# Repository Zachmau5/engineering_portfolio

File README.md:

# Zachary Hallett – Engineering Portfolio

Technical portfolio containing non-proprietary engineering projects focused on RF systems, satellite communications, DSP, embedded systems, FPGA development, scientific computing, and aerospace-related software development. The projects in this repository were developed through undergraduate electrical engineering research, independent technical work, and hands-on experimentation with real-world hardware and software systems.

---

# Areas of Interest

- RF Systems & SDR
- Satellite Communications
- Digital Signal Processing (DSP)
- Embedded Systems
- FPGA / VHDL Development
- Aerospace Systems
- Orbital Mechanics & Tracking
- Python Engineering Tools
- Real-Time Control Systems
- Linux-Based Engineering Workflows

---

# Repository Structure

```text
/amsat-ground-station
    Portable SDR-based amateur satellite tracking and ground station system

/kicad_projects
    Dump of personal KiCad designs and documents

---

# Featured Project – AMSAT Portable Ground Station

A portable dual-band amateur satellite ground station integrating:

- Automated antenna tracking
- Real-time orbit propagation
- SDR hardware integration
- RF subsystem analysis
- Autonomous azimuth/elevation control
- GUI-based visualization and tracking
- Satellite pass prediction
- Coordinate transformation pipelines
- Real-time tracking-control algorithms

## Key Technologies

- Python
- Skyfield / SGP4
- GNU Radio
- SDR platforms
- GS-232B rotator control
- RF front-end integration
- Real-time control systems

---

# Tools & Technologies

## Languages

- Python
- C / C++
- VHDL

## Engineering Tools

- LTSpice
- GNU Radio
- Vivado
- Git
- Linux
- KiCad

## Technical Areas

- SDR
- SATCOM
- DSP
- RF Analysis
- FPGA
- Embedded Systems
- Orbital Mechanics
- Real-Time Systems

---

# Notes

All material contained in this repository is non-proprietary and intended for educational, research, and portfolio purposes only. No export-controlled, classified, or employer-proprietary information is included.

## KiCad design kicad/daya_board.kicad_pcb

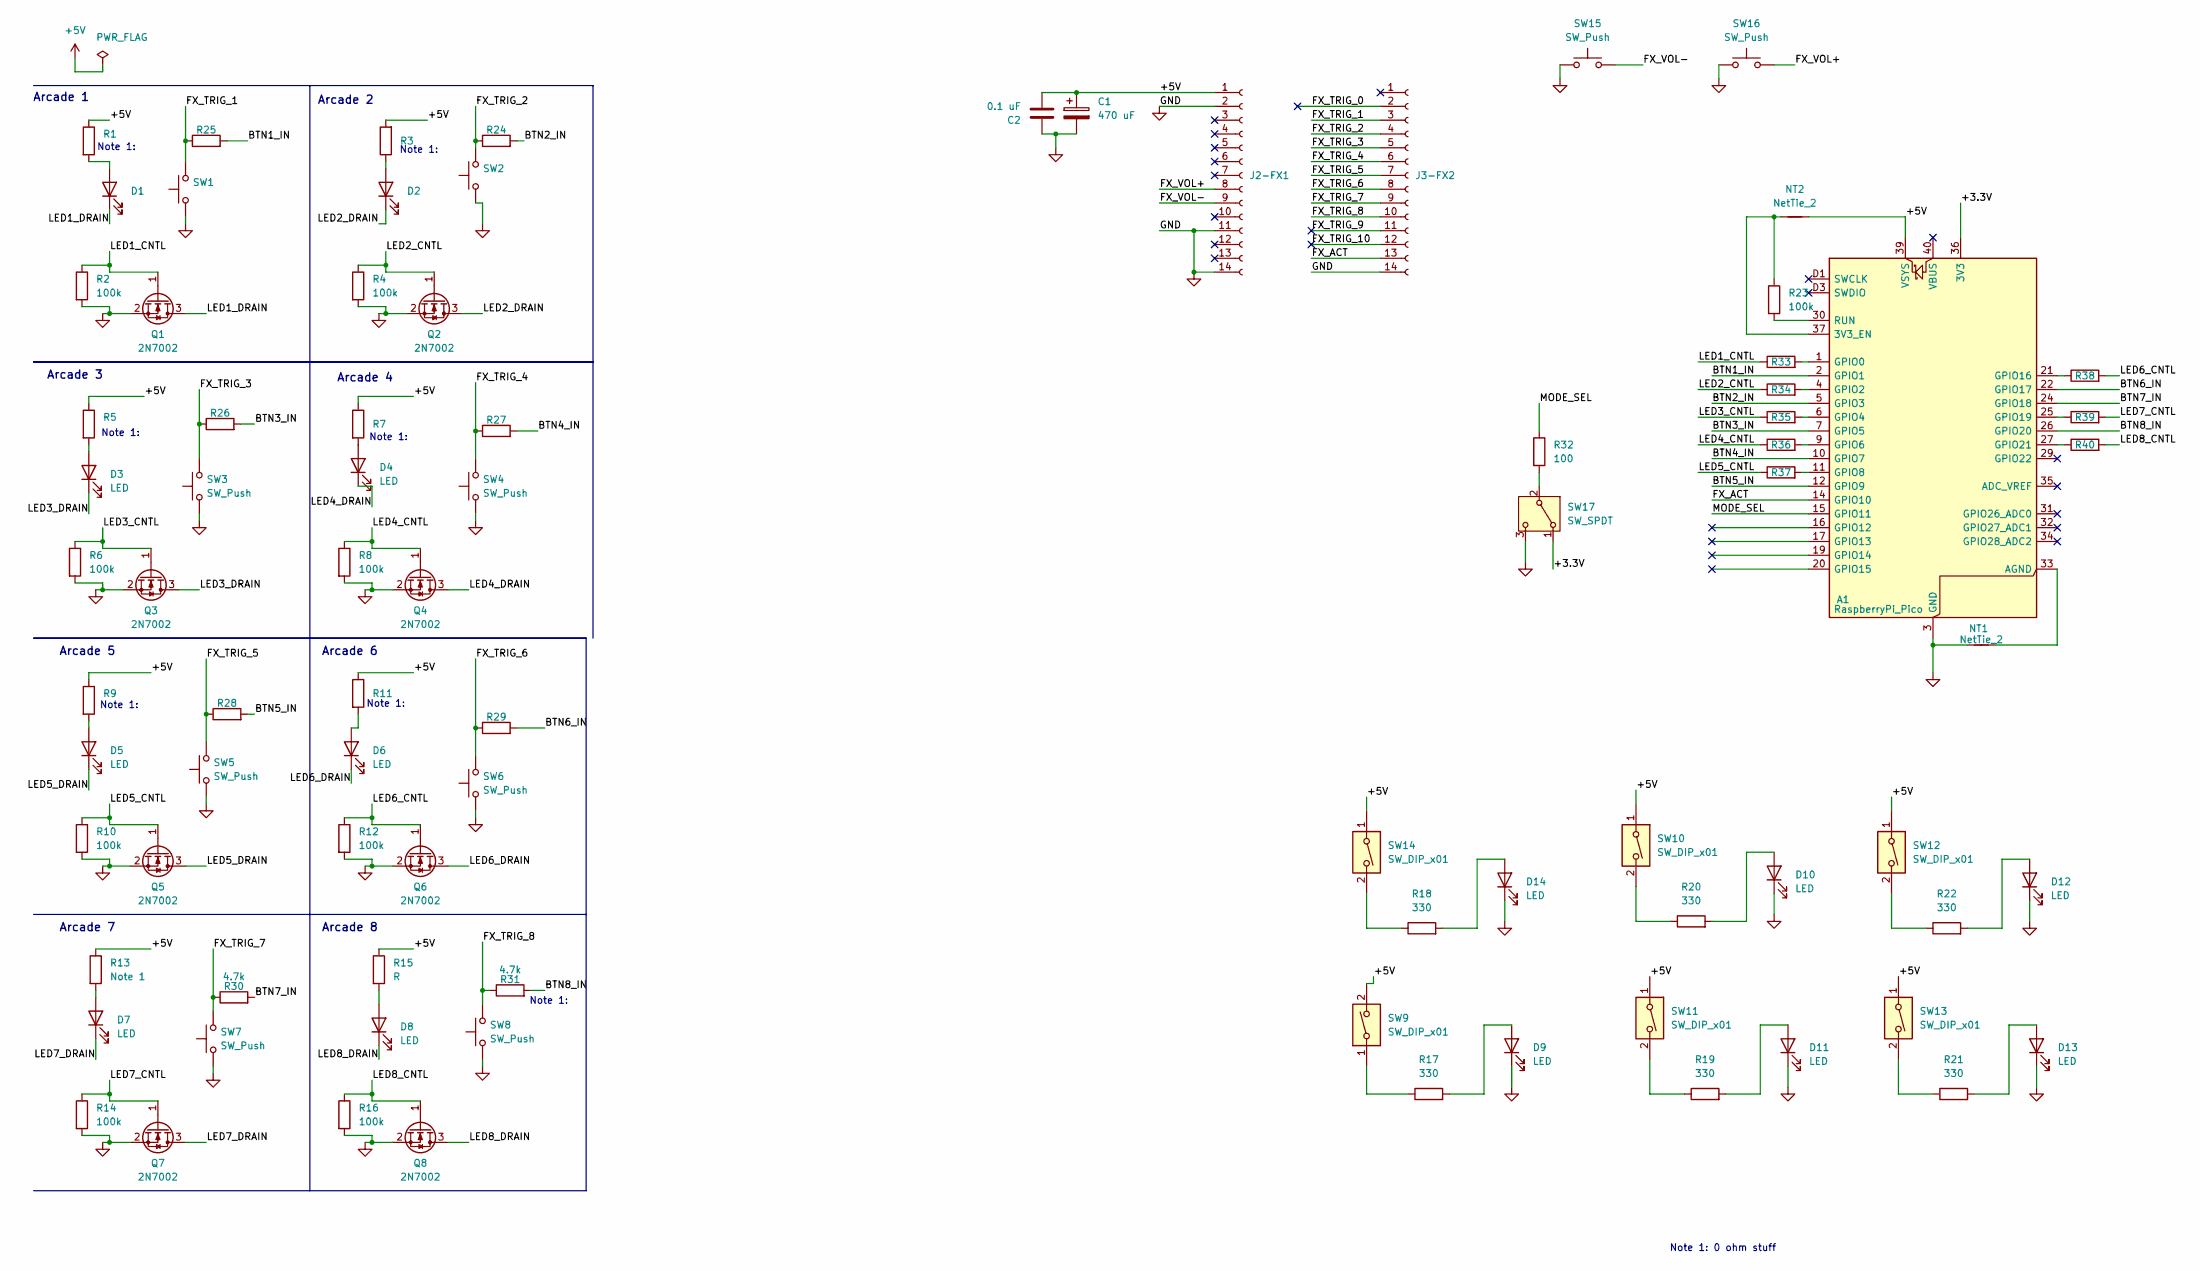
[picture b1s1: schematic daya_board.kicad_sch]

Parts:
A1: RaspberryPi_Pico; RaspberryPi_Pico_SMD_HandSolder
C1: 470 uF; CP_Radial_D8.0mm_P5.00mm
C2: 0.1 uF; C_Disc_D5.0mm_W2.5mm_P2.50mm
D1, D2, D3, D4, D5, D6, D7, D8, D9, D10, D11, D12, D13, D14: LED; JST_B2B-XH-A
J2-FX1, J3-FX2: Conn_01x14_Socket; PinHeader_1x16_P2.54mm_Vertical
NT1, NT2: NetTie_2; NetTie-2_THT_Pad0.3mm
Q1, Q2, Q3, Q4, Q5, Q6, Q7, Q8: 2N7002; SOT-23
R1, R3, R7, R9, R11: 0; R_Axial_DIN0207_L6.3mm_D2.5mm_P7.62mm_Horizontal
R2, R4, R6, R8, R10, R12, R14, R16, R23: 100k; R_Axial_DIN0207_L6.3mm_D2.5mm_P7.62mm_Horizontal
R5, R15: R; R_Axial_DIN0207_L6.3mm_D2.5mm_P7.62mm_Horizontal
R13: Note 1; R_Axial_DIN0207_L6.3mm_D2.5mm_P7.62mm_Horizontal
R17, R18, R19, R20, R21, R22: 330; R_Axial_DIN0207_L6.3mm_D2.5mm_P7.62mm_Horizontal
R24, R25, R26, R27, R28, R29, R30, R31: 4.7k; R_Axial_DIN0207_L6.3mm_D2.5mm_P7.62mm_Horizontal
R32, R33, R34, R35, R36, R37, R38, R39, R40: 100; R_Axial_DIN0207_L6.3mm_D2.5mm_P7.62mm_Horizontal
SW1, SW2, SW3, SW4, SW5, SW6, SW7, SW8, SW15, SW16: SW_Push; JST_B2B-XH-A
SW9, SW10, SW11, SW12, SW13, SW14: SW_DIP_x01; JST_B2B-XH-A
SW17: SW_SPDT; SW_Slide-03_Wuerth-WS-SLTV_10x2.5x6.4_P2.54mm

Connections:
+5V: A1.39 (VSYS), C1.1, C2.2, J2-FX1.1, NT2.2, R1.1, R3.2, R5.1, R7.1, R9.1, R11.1, R13.1, R15.1, SW9.2, SW10.1, SW11.1, SW12.1, SW13.1, SW14.1
/+3.3V: A1.36 (3V3), SW17.1 (A)
/BTN1_IN: A1.2 (GPIO1), R25.2
/BTN2_IN: A1.5 (GPIO3), R24.2
/BTN3_IN: A1.7 (GPIO5), R26.2
/BTN4_IN: A1.10 (GPIO7), R27.2
/BTN5_IN: A1.12 (GPIO9), R28.2
/BTN6_IN: A1.22 (GPIO17), R29.2
/BTN7_IN: A1.24 (GPIO18), R30.2
/BTN8_IN: A1.26 (GPIO20), R31.2
/FX_ACT: A1.14 (GPIO10), J3-FX2.13
/FX_TRIG_0: J3-FX2.2
/FX_TRIG_1: J3-FX2.3, R25.1, SW1.2
/FX_TRIG_2: J3-FX2.4, R24.1, SW2.2
/FX_TRIG_3: J3-FX2.5, R26.1, SW3.2
/FX_TRIG_4: J3-FX2.6, R27.1, SW4.2
/FX_TRIG_5: J3-FX2.7, R28.1, SW5.2
/FX_TRIG_6: J3-FX2.8, R29.1, SW6.2
/FX_TRIG_7: J3-FX2.9, R30.1, SW7.2
/FX_TRIG_8: J3-FX2.10, R31.1, SW8.2
/FX_TRIG_9: J3-FX2.11
/FX_TRIG_10: J3-FX2.12
/FX_VOL+: J2-FX1.8, SW16.2
/FX_VOL-: J2-FX1.9, SW15.2
/LED1_CNTL: Q1.1 (G), R2.1, R33.1
/LED1_DRAIN: D1.1 (K), Q1.3 (D)
/LED2_CNTL: Q2.1 (G), R4.1, R34.1
/LED2_DRAIN: D2.1 (K), Q2.3 (D)
/LED3_CNTL: Q3.1 (G), R6.1, R35.1
/LED3_DRAIN: D3.1 (K), Q3.3 (D)
/LED4_CNTL: Q4.1 (G), R8.1, R36.1
/LED4_DRAIN: D4.1 (K), Q4.3 (D)
/LED5_CNTL: Q5.1 (G), R10.1, R37.1
/LED5_DRAIN: D5.1 (K), Q5.3 (D)
/LED6_CNTL: Q6.1 (G), R12.1, R38.2
/LED6_DRAIN: D6.1 (K), Q6.3 (D)
/LED7_CNTL: Q7.1 (G), R14.1, R39.2
/LED7_DRAIN: D7.1 (K), Q7.3 (D)
/LED8_CNTL: Q8.1 (G), R16.1, R40.2
/LED8_DRAIN: D8.1 (K), Q8.3 (D)
/MODE_SEL: A1.15 (GPIO11), R32.1
GND: A1.3 (GND), A1.8 (GND), A1.13 (GND), A1.18 (GND), A1.23 (GND), A1.28 (GND), A1.38 (GND), A1.D2 (GND), C1.2, C2.1, D9.1 (K), D10.1 (K), D11.1 (K), D12.1 (K), D13.1 (K), D14.1 (K), J2-FX1.2, J2-FX1.11, J2-FX1.14, J3-FX2.14, NT1.1, Q1.2 (S), Q2.2 (S), Q3.2 (S), Q4.2 (S), Q5.2 (S), Q6.2 (S), Q7.2 (S), Q8.2 (S), R2.2, R4.2, R6.2, R8.2, R10.2, R12.2, R14.2, R16.2, SW1.1, SW2.1, SW3.1, SW4.1, SW5.1, SW6.1, SW7.1, SW8.1, SW15.1, SW16.1, SW17.3 (C)
unnamed: A1.37 (3V3_EN), NT2.1, R23.1
unnamed: A1.33 (AGND), NT1.2
unnamed: A1.1 (GPIO0), R33.2
unnamed: A1.4 (GPIO2), R34.2
unnamed: A1.6 (GPIO4), R35.2
unnamed: A1.9 (GPIO6), R36.2
unnamed: A1.11 (GPIO8), R37.2
unnamed: A1.21 (GPIO16), R38.1
unnamed: A1.25 (GPIO19), R39.1
unnamed: A1.27 (GPIO21), R40.1
unnamed: A1.30 (RUN), R23.2
unnamed: D1.2 (A), R1.2
unnamed: D2.2 (A), R3.1
unnamed: D3.2 (A), R5.2
unnamed: D4.2 (A), R7.2
unnamed: D5.2 (A), R9.2
unnamed: D6.2 (A), R11.2
unnamed: D7.2 (A), R13.2
unnamed: D8.2 (A), R15.2
unnamed: D9.2 (A), R17.2
unnamed: D10.2 (A), R20.2
unnamed: D11.2 (A), R19.2
unnamed: D12.2 (A), R22.2
unnamed: D13.2 (A), R21.2
unnamed: D14.2 (A), R18.2
unnamed: R17.1, SW9.1
unnamed: R18.1, SW14.2
unnamed: R19.1, SW11.2
unnamed: R20.1, SW10.2
unnamed: R21.1, SW13.2
unnamed: R22.1, SW12.2
unnamed: R32.2, SW17.2 (B)

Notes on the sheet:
Note 1:
Arcade 1
Arcade 6
Arcade 5
Arcade 8
Arcade 4
Arcade 7
Note 1: 0 ohm stuff
Arcade 2
Arcade 3

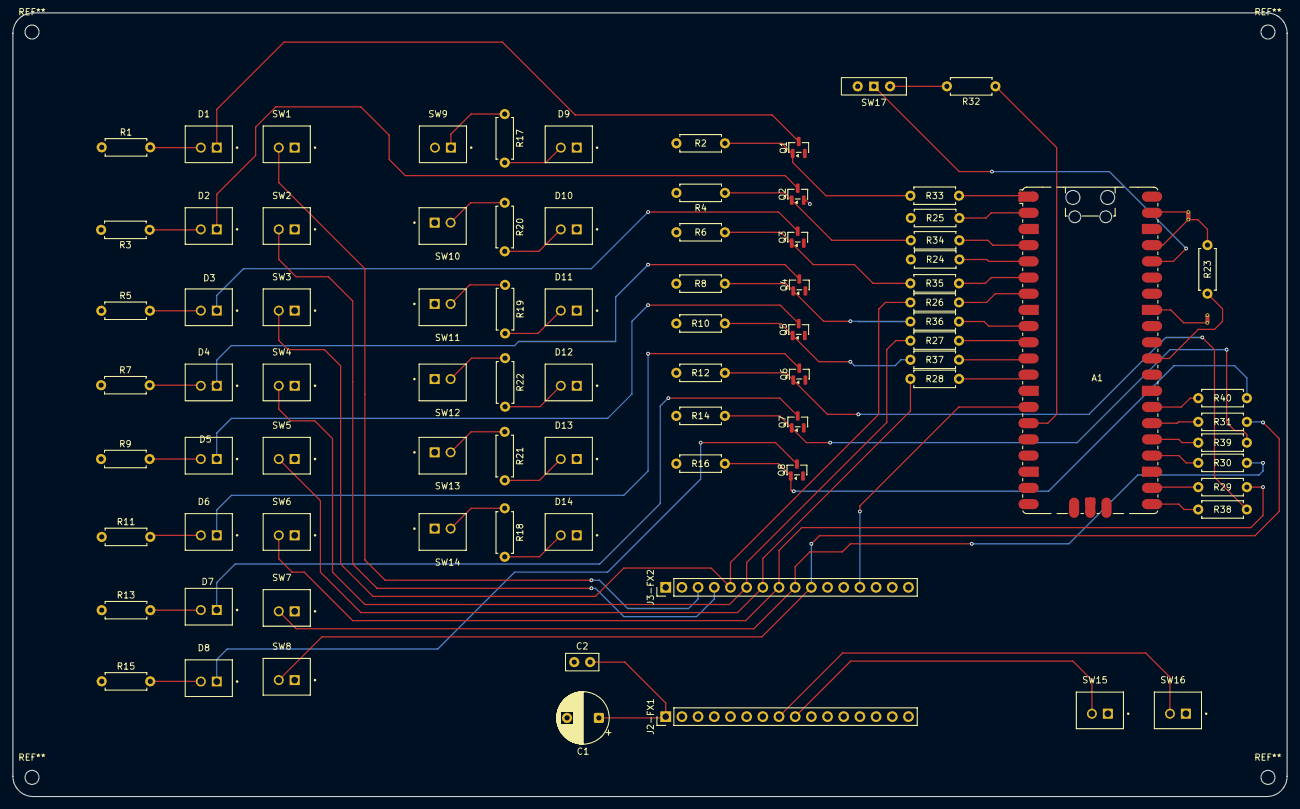
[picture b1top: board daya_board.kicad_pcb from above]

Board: 4 copper layers, 200.0 x 123.0 mm, 86 parts (0 on the bottom side), 71 nets.

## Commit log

2026-05-11 Create senior_design
2026-05-11 Update senior_design
2026-06-01 test
2026-06-01 temp
2026-06-01 daughter busy board
2026-06-01 upload pdf
